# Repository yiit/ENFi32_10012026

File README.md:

|Latest Nightly  | Build Status | Downloads | Docs | Patreon | Ko-Fi | PayPal |
|-------|-------|-------|-------|-------|-------|-------|
|  |  |  |  |  |  |  |

For ways to *support* us, see [this announcement on the forum](https://www.letscontrolit.com/forum/viewtopic.php?f=14&t=5787), or have a look at the [Patreon](https://www.patreon.com/GrovkillenTDer), [Ko-Fi](https://ko-fi.com/grovkillentder) or [PayPal](https://www.paypal.me/espeasy) links above.

# ESPEasy (development branch)

Introduction https://espeasy.readthedocs.io/en/latest/ (and, mostly outdated, wiki: https://www.letscontrolit.com/wiki/index.php/ESPEasy#Introduction)

**MEGA**
This is the development branch of ESPEasy. All new features go into this branch, and it has become the current stable branch. If you want to do a bugfix, do it on this branch.

Check here to learn how to use this branch and help us improving ESPEasy: [Starter guide for (local) development on ESPEasy](https://espeasy.readthedocs.io/en/latest/Participate/PlatformIO.html#starter-guide-for-local-development-on-espeasy)

## Web based flasher (experimental)

To make it easier to get started, one may flash a build directly to the ESP from your browser.
Currently only Chrome and Edge are supported.

See [this flash page](https://td-er.nl/ESPEasy/) to try the new web flash feature.

The web flasher is using [ESP Web Tools](https://esphome.github.io/esp-web-tools/) made by the people behind ESPHome and Home Assistant.

## Binary releases

On demand, controlled by the repo owner, our build-bot will build a new binary release: https://github.com/letscontrolit/ESPEasy/releases

The releases are named something like 'mega-20220626' (last number is the build date)

Depending on your needs, we release different types of files:

The name is built up from a few key parts:

ESPEasy_mega\_*[releasedate]*\_*[build-type]*\_*[opt-arduino-library]*\_*[hardware-type]*\_*[flash-size][filesystem-size]*\_*[opt-build-features]*.bin

*[build-type]* can be any of:
Build type   | Description                               | included plugins                 |
-------------|-------------------------------------------|----------------------------------|
climate A    | Plugins related to climate measurement A  | Stable + Climate A               |
climate B    | Plugins related to climate measurement B  | Stable + Climate B               |
custom       | Custom predefined set/Defined in Custom.h | Specific                         |
normal       | Standard plugins                          | Stable                           |
collection_A | Normal + plugin collection A              | Stable + Collection base + set A |
collection_B | Normal + plugin collection B              | Stable + Collection base + set B |
collection_C | Normal + plugin collection C              | Stable + Collection base + set C |
collection_D | Normal + plugin collection D              | Stable + Collection base + set D |
collection_E | Normal + plugin collection E              | Stable + Collection base + set E |
collection_F | Normal + plugin collection F              | Stable + Collection base + set F |
collection_G | Normal + plugin collection G              | Stable + Collection base + set G |
collection_H | Normal + plugin collection H              | Stable + Collection base + set H |
max          | All available plugins                     | All available                    |
energy       | All plugins related to energy measurement | Stable + Energy measurement      |
display A    | All plugins related to displays A         | Stable + Displays A              |
display B    | All plugins related to displays B         | Stable + Displays B              |
neopixel     | All plugins related to neopixel           | Stable + Neopixel                |
hard         | hardware specific builds                  | Minimal                          |
minimal      | minimal plugins for specific use-cases    | Switch and Controller            |
spec_*       | specialized technical builds              | Not intended for regular use     |
IRext        | Infra-red hardware specific               | Sending and receiving IR cmd     |
safeboot     | (Experimental) `safeboot` build to enable<br>most/all plugins on 4MB Flash boards | None                             |

*[opt-arduino-library]* (optional) can be any of:
Arduino library | Description                        |
----------------|------------------------------------|
alt_wifi        | Alternative WiFi configuration     |
beta            | Arduino Beta release               |
sdk3            | Arduino SDK v.3                    |
core_274        | Arduino Core 2.7.4 release         |
core_312        | Arduino Core 3.1.2 release         |
core_274_sdk3   | Arduino Core 2.7.4 SDK v.3 release |

*[hardware-type]* can be any of:
Hardware type    | Description                                 |
-----------------|---------------------------------------------|
ESP8266          | Espressif ESP8266/ESP8285 generic boards    |
WROOM02          | Espressif ESP8266 WRoom02 boards            |
ESP32            | Espressif ESP32 generic boards              |
ESP32solo1       | Espressif ESP32-Solo1 generic boards        |
ESP32s2          | Espressif ESP32-S2 generic boards           |
ESP32c3          | Espressif ESP32-C3 generic boards           |
ESP32s3          | Espressif ESP32-S3 generic boards           |
ESP32c2          | Espressif ESP32-C2 generic boards           |
ESP32c6          | Espressif ESP32-C6 generic boards           |
ESP32-wrover-kit | Espressif ESP32 wrover-kit boards           |
SONOFF           | Sonoff hardware specific                    |
other_POW        | Switch with power measurement               |
Shelly_1         | Shelly 1 switch                             |
Shelly_PLUG_S    | Shelly plug S switch with power measurement |
Ventus           | Ventus W266 weather station                 |
LCtech_relay     | LC-tech serial switch                       |

N.B. Starting 2022/07/23, 1M ESP8266 builds can also be used on ESP8285 units and thus there is no longer a specific ESP8285 build anymore.

*[flash-size]* can be any of:
Flash size | Description                 |
-----------|-----------------------------|
1M         | 1 MB with 128 kB filesystem |
2M         | 2 MB with 128 kB filesystem |
2M256      | 2 MB with 256 kB filesystem |
2M320k     | 2 MB with 320 kB filesystem |
4M1M       | 4 MB with 1 MB filesystem   |
4M2M       | 4 MB with 2 MB filesystem   |
16M        | 16 MB with 14 MB filesystem |
4M316k     | 4 MB with 316 kB filesystem |
8M1M       | 8 MB with 1 MB filesystem   |
16M1M      | 16 MB with 1 MB filesystem  |
16M8M      | 16 MB with 8 MB filesystem  |

N.B. Starting with release 2023/12/25, All ESP32 LittleFS builds use IDF 5.3, to support newer ESP32 chips like ESP32-C2 and ESP32-C6, and SPI Ethernet. Other SPIFFS based ESP32 builds will be migrated to LittleFS as SPIFFS is no longer officially available in IDF 5 and later. As a temporary solution, a specially crafted IDF 5.1 build that still includes SPIFFS, is used for the SPIFFS builds. A migration plan will be made available in 2025.

N.B.2 Starting with builds made after 2025/11/04, ESP32 builds will no longer have ``_LittleFS`` in the name as all ESP32 builds use LittleFS. Also the suffix ``_ETH`` has been removed since all builds will have Ethernet support, except for ESP32C2 builds.

*[opt-build-features]* can be any of:
Build features  | Description                                                                                               |
----------------|-----------------------------------------------------------------------------------------------------------|
LittleFS        | Use LittleFS instead of SPIFFS filesystem (SPIFFS is unstable \> 2 MB, and no longer supported in IDF \> 5) |
VCC             | Analog input configured to measure VCC voltage (ESP8266 only)                                             |
OTA             | Arduino OTA (Over The Air) update feature enabled                                                         |
Domoticz        | Only Domoticz controllers (HTTP) and plugins included                                                     |
Domoticz_MQTT   | Only Domoticz controllers (MQTT) and plugins included                                                     |
FHEM_HA         | Only FHEM/OpenHAB/Home Assistant (MQTT) controllers and plugins included                                  |
ETH             | Ethernet support enabled (ESP32 and IDF 5.x based builds)                                                 |
OPI_PSRAM       | Specific configuration to enable PSRAM detection, ESP32-S3 only                                           |
CDC             | Support USBCDC/HWCDC-serial console on ESP32-C3, ESP32-S2, ESP32-S3 and ESP32-C6                          |
noOTA/NO_OTA    | Does not support OTA (Over The Air-updating of the firmware) Use [the flash page](https://td-er.nl/ESPEasy/) or ESPTool via USB Serial |

N.B. Starting ca. 2025/02/27, many ESP32 builds are *only* available with _ETH suffix, indicating that Ethernet support is enabled, to reduce the (rather high) number of builds.

Some example firmware names:
Firmware name                                           | Hardware                                        | Included plugins                 |
--------------------------------------------------------|-------------------------------------------------|----------------------------------|
ESPEasy_mega-20230822_normal_ESP8266_1M.bin             | ESP8266/ESP8285 with 1MB flash                  | Stable                           |
ESPEasy_mega-20230822_normal_ESP8266_4M1M.bin           | ESP8266 with 4MB flash                          | Stable                           |
ESPEasy_mega-20230822_collection_A_ESP8266_4M1M.bin     | ESP8266 with 4MB flash                          | Stable + Collection base + set A |
ESPEasy_mega-20230822_normal_ESP32_4M316k_ETH.bin       | ESP32 with 4MB flash                            | Stable                           |
ESPEasy_mega-20230822_collection_A_ESP32_4M316k_ETH.bin | ESP32 with 4MB flash                            | Stable + Collection base + set A |
ESPEasy_mega-20230822_collection_B_ESP32_4M316k_ETH.bin | ESP32 with 4MB flash                            | Stable + Collection base + set B |
ESPEasy_mega-20230822_max_ESP32s3_8M1M.bin              | ESP32-S3 with 8MB flash, CDC-serial, Ethernet   | All available plugins            |
ESPEasy_mega-20230822_max_ESP32s3_8M1M_OPI_PSRAM.bin    | ESP32-S3 8MB flash, PSRAM, CDC-serial, Ethernet | All available plugins            |
ESPEasy_mega-20230822_max_ESP32_16M1M_ETH.bin           | ESP32 with 16MB flash, SPIFFS, Ethernet         | All available plugins            |
ESPEasy_mega-20230822_max_ESP32_16M8M.bin               | ESP32 with 16MB flash, LittleFS, Ethernet       | All available plugins            |

The binary files for the different ESP32 variants (S2, C3, S3, C2, C6, Solo1, 'Classic') are available in separate archives.

To see what plugins are included in which collection set, you can find that on the [ESPEasy Plugin overview page](https://espeasy.readthedocs.io/en/latest/Plugin/_Plugin.html)

For ESP32 builds (all models) there are 2 ``.bin`` files available:
1) a ``.factory.bin`` to be used when flashing the firmware via external tools, like the Espressif Flash Download tool, to be loaded at address ``0x0``, that includes the bootloader and flash-partitioning data. This is the second of 2 recommended methods to install ESPEasy on a new device.<BR/>
The main recommended method for flashing ESPEasy onto a (new) device is via [this flash page](https://td-er.nl/ESPEasy/) (using Chrome or Edge webbrowser), where you connect the device via USB-serial, and select what firmware-build to install.
2) a 'regular' ``.bin`` file, that can be used to update a running board via OTA (Over The Air), using the Update Firmware button on the Tools page. The .bin file then has to be available for the device the webbrowser is running from (local or via a network), as the file is uploaded via the webbrowser.<BR/>
The firmware to upload via OTA must match both the ESP32 model, and current partitioning & formatting, LittleFS as indicated in the name, or SPIFFS.

## Documentation & more info

Our new, in-depth documentation can be found at [ESPEasy.readthedocs.io](https://espeasy.readthedocs.io/en/latest/). Automatically built, so always up-to-date according to the contributed contents. The old Wiki documentation can be found at [letscontrolit.com/wiki](https://www.letscontrolit.com/wiki/index.php?title=ESPEasy).

Additional details and discussion are on the "Experimental" section of the forum: https://www.letscontrolit.com/forum/viewforum.php?f=18

## SAST Tools

[PVS-Studio](https://pvs-studio.com/en/pvs-studio/?utm_source=website&utm_medium=github&utm_campaign=open_source) - static analyzer for C, C++, C#, and Java code.

## Icons used

Icons on courtesy of [ICONS8](https://icons8.com/).

# Senin Tarafýndan Yapýlan Deðiþiklik
# ENFi32 - Yeni Proje

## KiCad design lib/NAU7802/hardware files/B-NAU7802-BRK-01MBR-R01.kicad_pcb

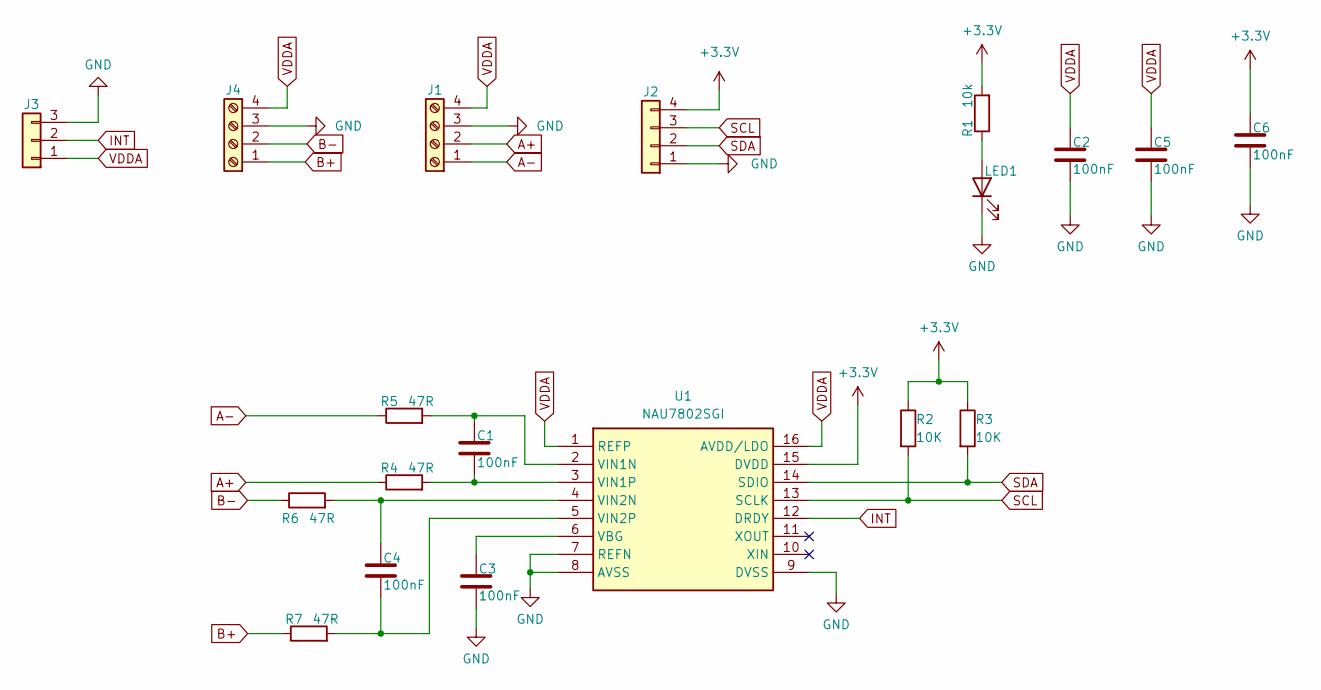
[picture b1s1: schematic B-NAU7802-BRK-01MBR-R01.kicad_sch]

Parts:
C1, C2, C3, C4, C5, C6: 100nF; C_0603_1608Metric; MPN CL10B104KB8NNNC
J1, J4: Screw_Terminal_01x04; TerminalBlock_MetzConnect_Type059_RT06304HBWC_1x04_P3.50mm_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; MPN DG350-3.5-02P-14-00AH
J2: Conn_01x04; 2317-04S_1x04_P2.50mm_Vertical
J3: Conn_01x03; PinHeader_1x03_P2.54mm_Vertical; MPN L-KLS1-207-1-03-S
LED1: RedPower; LED_0603_1608Metric; MPN 19-213USRC/S259/TR8
R1: 10k; R_0603_1608Metric; MPN 0603SAJ0103T5E
R2, R3: 10K; R_0603_1608Metric; MPN 0603SAJ0103T5E
R4, R5, R6, R7: 47R; R_0603_1608Metric; MPN CQ03SAJ0470T5E
U1: NAU7802SGI; SOIC127P600X175-16N; Manufacturer_Part_Number NAU7802SGI

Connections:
+3.3V: C6.1, J2.4, R1.2, R2.1, R3.1, U1.15 (DVDD)
A+: J1.2, R4.1
A-: J1.1, R5.1
B+: J4.1, R7.1
B-: J4.2, R6.1
GND: C2.2, C3.2, C5.2, C6.2, J1.3, J2.1, J3.3, J4.3, LED1.1 (K), U1.7 (REFN), U1.8 (AVSS), U1.9 (DVSS)
INT: J3.2, U1.12 (DRDY)
unnamed: LED1.2 (A), R1.1
unnamed: C3.1, U1.6 (VBG)
unnamed: C1.1, R5.2, U1.2 (VIN1N)
unnamed: C1.2, R4.2, U1.3 (VIN1P)
unnamed: C4.1, R6.2, U1.4 (VIN2N)
unnamed: C4.2, R7.2, U1.5 (VIN2P)
SCL: J2.3, R2.2, U1.13 (SCLK)
SDA: J2.2, R3.2, U1.14 (SDIO)
VDDA: C2.1, C5.1, J1.4, J3.1, J4.4, U1.1 (REFP), U1.16 (AVDD/LDO)

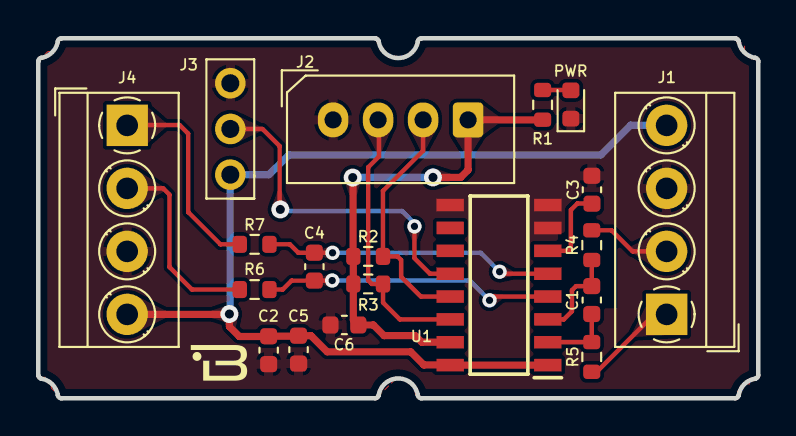
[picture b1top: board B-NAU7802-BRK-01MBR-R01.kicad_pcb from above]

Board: 2 copper layers, 40.0 x 20.0 mm, 19 parts (0 on the bottom side), 16 nets.

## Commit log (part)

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2025-06-08 [UoM] Add Unit of measure value to /json endpoint
2025-06-08 [Build] Include reboot.js script in readable form
2025-06-08 [UoM] Make .js script more fault tolerant when no global UoM enable setting is available
2025-06-10 [UoM] Add Feature TaskValue-attributes with support for .uom, .decimals, .hasformula and .statsenabled
2025-06-12 [UoM] Add documentation
2025-06-14 [ValueTypes] Add Custom VType selection
2025-06-17 Update LD2410 doc adding info of false positive
    Update LD2410 doc adding info of avoid false positive
2025-06-19 [C014] Add Unit of Measure to AutoDiscovery, add Send Derived values support
2025-06-20 [ESP-IDF] Revert to older build due to broken UART support
2025-06-20 [build] Change ESP32 IRExt builds to LIMIT_BUILD_SIZE
2025-06-21 [Docs] Update docs for Value Type setting for selected plugins
2025-06-21 [Derived Values] Move enable sending per task-controller, Code optimization
2025-06-23 [ESP32-C61] Start adding support for new SoC & generalize WiFi features
2025-06-23 [ADC] Fix not setting attenuation on internal ADC
2025-06-25 [MFRC522] Simplify board reset during init
2025-06-25 [ESP32-S3] Revert changes in board defines for ESP32-S3 with OPI PSRAM
2025-06-26 [Rules] Fix processing variables with index > 2^31
2025-06-26 [MFRC522] Speedup reading by acting on interrupt pin
2025-06-26 [MFRC522] Do proper timing for communicating with card
2025-06-26 [PWM motor] Speedup acting on limit switch interrupt
2025-06-28 [Plugins] Minor code improvement
2025-06-28 [AutoDiscovery] Update PluginTemplate
2025-06-28 [PubSubClient3] Speedup publish large messages using buffer
    As discussed here: https://github.com/hmueller01/pubsubclient3/issues/29#issuecomment-2727644476
2025-07-03 [Controller] Fix crashes on MQTT callback calls
2025-07-05 [Network] Start adding Network config page
2025-07-06 [AutoDiscover] Refactor discovery message composition to reduce binary size by nearly 4k
2025-07-06 [Network] Start on initial first WiFi STA/AP drivers
2025-07-07 [ESP32P4] Add preliminary support for ESP32P4
2025-07-08 Fix horizantal vane not working
2025-07-09 [ESP32P4] Add more warnings for specific GPIO pins
2025-07-09 [Network] Add ETH config page + tweak Network Page
2025-07-11 [PPP Modem] Add framework for new PPP Modem network interface
2025-07-12 [AutoDiscover] Clean names sent to HA by replacing unsupported characters by `_`
2025-07-12 [Converters] Make system time-zone optional in `%c_ts2isodate%()` (second argument != 0)
2025-07-12 [AutoDiscover] Remove non-working `Date/Time` (`datetime`) Device class :-(
2025-07-13 [P176] Set default Value Types when adding the plugin
2025-07-13 [Network] Add NetworkSettings type to store network interface settings
2025-07-15 [Storage] Fix issues storing/loading from key/value store
2025-07-15 [Storage] Use key value store for storing network interfaces
2025-07-16 [PPP modem] Remove PPP Modem plugin from ESP32-C3 as there isn't support
2025-07-17 [PPP Modem] Add UE Cell info + fix ESP32C2 build
2025-07-17 [AutoDiscover] Try to get switch trigger working
2025-07-17 [Network] Allow crash detection to turn off network interfaces
2025-07-19 [Storage] Fix storing bool types
2025-07-19 [Network] Add WiFi/AP when not present in settings + limit options
2025-07-20 [MQTT] Fix command handling for /set and /cmd topic endpoints, add support for P001 in /set
2025-07-21 Update espeasy.js
    simple On-Do-Endon and If-Endif checks
2025-07-21 format even without colorcode enabled
2025-07-21 more robust block checks
2025-07-21 jump to line of first error and keep history
2025-07-22 [Metrics] Update documentation
2025-07-24 fixed broken replace function
2025-07-24 find while typing
2025-07-25 removed unnecessary function
2025-07-26 [AutoDiscover] Fix P021 not to be handled as a Switch
2025-07-26 [Network] Move global runtime data to new ESPEasy::net namespace
2025-07-27 [Network] Move more WiFi related code into ESPEasy::net::wifi namespace
2025-07-27 [Network] Move Network code to ESPEasy::net namespace
2025-07-27 as good as it gets :)
    - support for chrome, vivaldi and firefox on android (hopefully)
2025-07-27 [Network] Fix setting up last network/controller entry
2025-07-28 fix: jump back to cursor position after formatting
2025-07-30 [TaskValueSetDerived] Improved parsing of Unit of Measure value
2025-07-31 [Tasks] Fix scheduled Plugin Task Timer & proper task exit/init
2025-08-01 [Network] Fix ESP8266 build + add log when DNS is restored from cache
2025-08-02 Update _P078_Eastron.ino with changelog info
2025-08-03 [Network] Move common code to collect connection stats to base class
2025-08-03 missing import os
2025-08-04 remove cache use uv
2025-08-04 Update P078_data_struct.cpp - added nat:load to SDM_UOMtoString strings
2025-08-04 Update P078_data_struct.cpp - updated register addresses for the last 5 registers of TAC2100
2025-08-04 [P078] Improved value descriptions and register appended, small code improvements
2025-08-04 [Network] Clean up code duplication handling network events
2025-08-05 disable shortcuts
2025-08-06 [P102] UI updates and corrections
2025-08-07 [BusCmd I2C] Add support for handling > 128 bytes on I2C read/write (ESP32)
2025-08-07 [BusCmd Helper] Send data & event when updating value.N from other than PLUGIN_READ action
2025-08-08 [AutoDiscover] Update documentation for Group setting
2025-08-09 [Network] Cleanup + add charts for RSSI/TX-pwr, traffic, etc.
2025-08-10 [Build] Reduce build size on ESP8266 builds
2025-08-10 [Network] Fix corrupting settings on ESP8266
2025-08-13 [Network] Fix access control check for accessing web config
2025-08-13 [Network] Fix NAPT forwarding when client connects/disconnects
2025-08-14 [P089] Add support for ESP32
2025-08-16 [P180] Add optional skip argument to IF I2C command, update docs
2025-08-19 [MFRC522] Speedup reading tag
2025-08-21 [Network] Add AT command write to PPP modem
2025-08-21 [P168] Update documentation
2025-08-23 [MQTT] Handle connecting to broker as a background process
2025-08-26 [MQTT] Reconnect on unexpected network interruptions
2025-08-27 [Discovery] Avoid setting the timeout more than once
2025-08-31 [ESP-IDF] Move to IDF5.5 for all ESP32-xx builds
2025-09-02 [USBCDC] Fix USB-CDC for ESP32S2 builds
2025-09-04 [MQTT] Refactor background connection process to avoid logging from background task
2025-09-08 [P089] Bugfix: Putt include in scope
2025-09-12 [WiFi] Fix WiFi reconnect issues
2025-09-12 [P033] Update documentation
2025-09-15 [C011] HTTP Advanced - Don't URL-encode header
2025-09-18 [SysVars] Fix showing variables with hex number as index
2025-09-18 [LAN867x] Add support for LAN867x Ethernet controller (RMII)
2025-09-21 [Network] Fix showing stats and connection info
2025-09-22 [Eth] Clear uses of EthEventData for ESP32 builds
2025-09-23 [WiFi] Fix wifi reconnect (on ESP32)
2025-09-24 [NeoPixel] Make NeoPixelSendStatus use less memory allocations
2025-09-24 [CSS] Tweaks for newly added Network tab
2025-09-24 [MQTTDiscovery] Reduce mem alloc MQTT_DiscoveryPublishWithStatusAndSet
2025-09-25 [WiFi AP] Fix switching between NAPT and Captive Portal
2025-09-27 [Provision] Fix not able to provision files
2025-09-29 [CacheReader] Fix reading cache files from CacheController
2025-09-29 [CacheReader] Fix continue reading after crash/reboot
2025-09-30 [CacheReader] Fix reading cache files when files are missing
2025-10-02 [Log] Use new streaming JSON writer to generate web log
2025-10-03 [Build] Fix compiler warning
2025-10-03 [JSON] Use new createChild function
2025-10-04 [Build] Enable BUILD_NO_DEBUG for 2nd heap ESP8266 normal builds
2025-10-05 [Cleanup] Reduce bin size: unsigned long to uint32_t and long to int32_t
2025-10-05 [Network] Cleanup code + generate more network info using new K/V writer
2025-10-06 [Build] Reduce bin size by disabling logs in BUILD_NO_DEBUG builds
2025-10-06 [Build] Fix build errors on RISC-V like ESP32-C2/C3/C5/C6
2025-10-07 [ESP-IDF] Update to latest Arduino/ESP-IDF
2025-10-09 [Log] Simplify web log buffering
2025-10-10 [WebLog] Send many log messages in chunks of 200 msec.
2025-10-10 [TimingStats] Add stat to measure time spent processing MQTT messages
2025-10-13 [TLS-MQTT] Automatic switch to ECDSA when error is 296 (TLS handshake)
2025-10-14 [Log] Serial Console pulls logitems when UART buffer is ready + colorize
2025-10-16 [Log] Make syslog to use the new log queue + fix syslog crashes
2025-10-17 [Cleanup] Rename Sp_KeyValueWriter to Up_KeyValueWriter
2025-10-18 [HTTP] Update documentation for TLS options
2025-10-18 [Climate] Remove P169 (AS3935 lightning Detector) from ESP8266 builds
2025-10-20 [PPP modem] Show mobile provider name from SIM card
2025-10-21 [KeyValueStruct] Add standard Unit-of-Measure units
2025-10-22 [ChartJS] Make charts appear on the full width and responsive
2025-10-24 [Build] Reduce build size by disabling GitHub copy button for ESP8266
2025-10-25 [Units Of Measure] fix merge issues PR #5419
2025-10-26 [ESP32P4] Disable USB HWCDC to fix ESPEasy console for ESP32P4
2025-10-26 [Build] Remove obsolete comments
2025-10-26 [ETH] Remove left-over code duplication after split RMII/SPI adapters
2025-10-27 [ESPEasy Console] Fix console on both HWCDC and Serial0
2025-10-27 Bump actions/upload-artifact from 4 to 5
    Bumps [actions/upload-artifact](https://github.com/actions/upload-artifact) from 4 to 5.
    - [Release notes](https://github.com/actions/upload-artifact/releases)
    - [Commits](https://github.com/actions/upload-artifact/compare/v4...v5)
    ---
    updated-dependencies:
    - dependency-name: actions/upload-artifact
2025-10-27 [Build] Avoid build-reduction for MAX builds
2025-10-28 [Ethernet] Add already setup Ethernet when upgrading ESPEasy
2025-10-29 [Network] Add NetworkImportConfig command
2025-11-04 [ESP-IDF] Update to latest Arduino/IDF code with fix for SPI Eth MAC
2025-11-05 [ESP32-P4] Disable OTA update for ESP-HOSTED-MCU on ESP32P4 for now
2025-11-05 [Web Flasher] Update script to generate webflasher for new build names
2025-11-09 [Ethernet] Fix loading SPI Ethernet settings from KVS
2025-11-10 [UI] Update addTaskSelector() to use FormSelectorOptions
2025-11-17 [Build] Speed up builds, add not used libs to lib_ignore
2025-11-17 [PluginList] Update for HTTPS TLS support
2025-11-17 [ESPEasy p2p] Add IDs of not yet supported ESP MCUs
2025-11-21 [WiFi] Fix check for available credentials only in device specific file
2025-11-23 [AutoDiscovery] Show Auto Discovery for Controllers that have this enabled (Task configuration)
2025-11-25 [Bugfix] Calculation missed value when returning from multiple brackets
2025-11-27 [Cleanup] Mark unused members in SettingsStruct
2025-12-01 [WiFi] Simplify WiFi AP fallback scenarios
2025-12-04 [C023] Clone C018 code to C023
2025-12-04 [SysVars] Documentation for %latitude% and %longitude% vars and Latitude and Longitude commands
2025-12-10 [C023] Add option to trigger events via downlink messages + code cleanup
2025-12-13 [Rules] Add some functions, conversions and constants
2025-12-13 [WiFi] Add link to ESP-Hosted-MCU firmware builds
2025-12-19 [Bugfix] Metrix: Export 0 for empty values
2025-12-23 [P087] Add support for receiving binary data, fixed length data, and event as hex string
2025-12-29 [P004] Change name to include DS18xxx/MAX31xxx for better recognizability
2026-01-05 [USBCDC] Simplify code defining USBCDC(TinyUSB) vs. HWCDC
2026-01-06 [WiFi] Fix reconnecting when connection gets interrupted
2026-01-08 [Build] Add flags to disable webserver JSON or syslog to reduce bin size
2026-01-12 Feature: README güncellendi
2026-01-12 Feature: P200 NAU7802 24-bit Scale Plugin - Terazi modülü
    - Zero calibration (Tare)
    - Load cell calibration
    - Maximum capacity setting
    - Decimal place resolution
    - Smoothing/averaging filter
    - Measurement speed control (10Hz-80Hz)
2026-01-12 Refactor: P200 plugin'i NAU7802 kütüphanesini doğru şekilde kullan
    - NAU7802.h header'ını include et
    - NAU7802 sınıfını direkt kullan (Wire yerine)
    - Kütüphanenin API'sini kullan: begin(), powerUp(), readADCValue(), setGain(), setSampleRate()
    - Yeni komutlar: p200gain, p200rate
    - Calibration factor hesaplaması düzeltildi
    - Memory yönetimi iyileştirildi (new/delete)
